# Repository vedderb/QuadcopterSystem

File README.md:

# The SP Quadcopter System

This is the source code and hardware design for a quadcopter system that was developed at SP Technical Research Institute of Sweden in the department of electronics as a demonstrator within the EU Projects KARYON and PROWESS.

Figure 1 shows an overview of the quadcopter system and how everything is connected.

The system consists of:

* Quadcopters
	- We have used up to 4 quadcopters simultaneously.
	
* [Anchors](#anchors)
	- For localization in GNSS-denied areas.
	- 2, 3 or 4 anchors can be used. When 4 anchors are used, the system can still operate if at least one of them or at most two of them fail due to redundancy.
	
* A Linux computer with two [stm32-bv motes](http://vedder.se/2013/04/cc2520-and-stm32-rf-boards/).
	- [QuadcopterTool](#quadcoptertool) is used for real time display and sending control commands to the quadcopters.
	- A border router is used to synchronize the clocks of all quadcopters and [anchors](#anchors) to microsecond level for ultrasound localization and TDMA communication.

* A [simulator](#coptersim) for the quadcopter system
	- The quadcopters and the localization system are simulated.
	- Can send the state of the simulation over UDP to [QuadcopterTool](#quadcoptertool) for visualization.
	- Cooperative collision avoidance is implemented in the simulator.

The following parts are included with this repository:

* **Embedded** - software running on the microcontrollers of the quadcopter system.
	- **border_router_clock_sync** - A contiki border router that also sends out clock synchronization packets (running on *stm32-bv with Contiki* in the next Figure).
	- **QuadcopterMain** - Main control software for the quadcopters (running on the *Mainboard*).
	- **Range** - Software for the *Ranging Board* and the anchors.
	- **Receiver** - Running on *stm32-bv with ChibiOS* in the next Figure and on a modified remote controller.
	- **Lib** - ChibiOS and Contiki
* **Linux** - software running on a GNU/Linux distribution (e.g. Ubuntu) for configuration, control and simulation.
	- **CopterSim** - A [simulation library](#coptersim) for the quadcopter system.
	- **CopterSimGui** - Graphical user interface for the [CopterSim](#coptersim) library
	- **FaultCheck** - Fault Injection Library used in [CopterSim](#coptersim) and [CopterSimGui](#coptersimgui)
	- **magnetometer_calibration** - Octave scripts for soft and hard iron compensation on the magnetometer.
	- **QuadcopterTool** - Graphical user interface for control and real time visualization of the quadcopter platform.
	- *build* - Script for building everything.
	- *clean* - Script for removing all built files.
	- *set_env* - Script used by the other scripts for setting the required environment variables.
	- *start_QuadcopterTool* - Script for starting [QuadcopterTool](#quadcoptertool).
	- *start_sim* - Script for starting [CopterSimGui](#coptersimgui) (that uses [CopterSim](#coptersim) and FaultCheck) and [QuadcopterTool](#quadcoptertool) for visualizing the simulation.
* **Hardware** - hardware design files
	- **MainBoard** - Design files for the MainBoard and Ranging Board PCBs
* **Documentation**
	- **Figures** - The figures in the documentation.
	- **Figures_pdf_png** - Png versions of all PDF files for including them in markdown
	- **PDF** - The documentation rendered as PDF files.
	- *conv_png* - Script for converting all PDF figures to PNG images.
* *build_doc* - Script for generating PDF files of the documentation.

A tutorial on how to get everything running can be found [here](Tutorial.md) (or [here](Tutorial.pdf) as pdf).

## Hardware on each Quadcopter

The hardware architecture on each quadcopter is shown in Figure 2.

Each quadcopter has two custom hardware-wise identical computing nodes connected over CAN-bus. The schematic and hardware layout, as well as the source code, for these computing nodes is included with this repository.

The Mainboard uses the [ChibiOS 3.x](http://www.chibios.org) RTOS, and runs the attitude control loop, position estimation, position control and interfaces with [QuadcopterTool](#quadcoptertool) over its radio link. The motors are connected to the Mainboard. More details about the software on the Mainboard can be found in the section [Mainboard Software](#mainboard-software).

The Ranging Board (RB) runs a [custom port](http://vedder.se/2013/10/a-contiki-port-for-my-custom-cc2520stm32f4-boards/) of [Contiki OS](http://www.contiki-os.org/) and is responsible for localization. The RB has a synchronized clock with the [anchors](#anchors) (provided by the border router) and measures the distance to them using the Time of Flight of ultrasound pulses sent from the anchors. In order to reject noise, the pulses are modulated using the sinc function and identified using cross correlation on sampled signal on the RB. An ultrasound height sensor is also connected to the RB that measures the distance from the quadcopter to the ground. All measured distances and the synchronized clock are sent over CAN-bus to the Mainboard for processing. Notice that the quadcopters can be controller manually without connecting the ranging board if desired.

A photo of the Main Board is shown in Figure 3.

## Mainboard Software
The important software on the MainBoard consists of the following parts:

**actuator**  
Translates throttle, roll, pitch and yaw output to commands for the motors. Compensation for varying input is also applied here.

**broadcast**  
Broadcast status and safety messages to the other quadcopters and to [QuadcopterTool](#quadcoptertool). The status message, used by [QuadcopterTool](#quadcoptertool), contains:

* Quadcopter ID
* Firmware Version
* Position (X, Y, Z)
* Attitude (roll, pitch, yaw)
* Velocity (vx, vy)
* Battery voltage
* Voltages sampled on the ADC port

The safety message (which will not be covered in detail in this description yet) contains:

* Quadcopter ID
* Local level of service
* Global level of service

To not get interference, these messages are sent out using TDMA based on the quad ID and the global clock provided by the ranging board.

**control**  
The attitude control loop.

**mpu9150** and **MahonyAHRS**  
Reading and processing of the accelerometer, gyroscope and magnetometer signals to calculate the filtered attitude of the quadcopter.

**navigation**  
The position control loop.

**pos**  
Position estimation based on the quadcopter attitude, [anchor](#anchors) readings and the motor power output (which for now is assumed to be 1g vertical acceleration).

**safety**  
Level of service calculation of the quadcopter (local) and all quadcopters (global).

**packet_handler**  
The communication protocol between QuadcopterTool and the quadcopters.

**Makefile**  
A makefile for building the software on the mainboard.

## QuadcopterTool

QuadcopterTool is a GUI to visualize and send commands to the quadcopter system. The main control page is shown in Figure 4. There are several pages for control, configuration and visualization, and the lower part of QuadcopterTool shows which quadcopters are sent status messages the past second together with their firmware version and battery level.

Figure 5 shows how the raw accelerometer, gyroscope and magnetometer values are plotted in real time in QuadcopterTool.

Figure 6 shows how one quadcopter is displayed on a map in real time in QuadcopterTool. 4 [anchors](#anchors) are also shown and a red bounding box where the quadcopter is allowed to fly. The [anchor](#anchors) positions and the bounding box can be edited and uploaded to the quadcopters from QuadcopterTool for the localization to work.

## Anchors

The quadcopter system uses anchors that send ultrasound pulses to the quadcopters for measuring the distance to them. This is done based on the time of flight of the ultrasound pulses which can be measured by having a synchronized clock between the quadcopters and anchors. This system is used for localization in GNSS-denied areas. A photo of the anchors is shown in Figure 7.

Figure 8 shows three quadcopters, three anchors and the distances measured between them. The quadcopters know the locations of all anchors, which are configured via [QuadcopterTool](#quadcoptertool).

To reject noise, the ultrasound pulses are modulated sinc functions and the Ranging Board does cross correlation between the samples signal and the expected pulse shape. Figure 9 shows the raw sampled signal and the cross correlation result when measuring a distance of around 10m. It can be seen that the cross correlation rejects almost all noise until the actual pulse (and its reflections) is received. To get the direct path and not a reflection that might be stronger, the Ranging Boards looks for the first top above a certain threshold and not the highest top.

If no pulse above with an amplitude above the threshold is received, the measurement from that anchor is ignored. This way, the system can still operate when one or two anchors fail (if there are enough anchors from the beginning).

## CopterSim

CopterSim is a library written in C++ with an interface where quadcopters can be added, removed, or commanded to move. A block diagram of the simulator is shown in Figure 10.

The block named *CopterSim* has a list of *CopterModels* and a list of line segments that represent static terrain. For every time-step dt, CopterSim executes the state update function for each CopterModel and checks for collisions between all CopterModels and the static terrain. When a collision occurs, the simulation is halted and the position of the collision is reported. When a CopterModel is added to the simulation, CopterSim will upload the list of terrain to it and broadcast perceived position state messages from it to the other CopterModels and vice versa. This broadcast is done between all quadcopters every communication time interval and the messages are passed through the communication channel of FaultCheck, where communication faults can be injected.

The *CopterModel* block runs the same source code for position and velocity estimation as the implementation on the embedded implementation. The attitude is updated from the movement command with a similar response to that of the actual hardware, and the golden run (the fault-free position and velocity state) is updated based on this attitude. In addition to the true position state for each quadcopter, CopterModel also updates the perceived position for them. For the perceived position, we have added FaultCheck probes to the various state variables where faults can be injected. As long as no fault is activated, the true and perceived position will be the same. As soon as we activate faults, the positions will drift apart.

In order to compensate for faults and thus position drift, the perceived position has to be estimated using ultrasound sensor readings. CopterModel is aware of all anchors and emulates ultrasound-sensor readings based on the true position state and the anchor positions, with the same rate as they are received on the hardware quadcopters. These readings are passed to the correction part of the position-estimation algorithm, which then corrects the position.

Every CopterModel has a block named ITS station, which builds and updates a Local Dynamic Map (LDM) that contains all other quadcopters and their states as it receives messages from them. The ITS station also keeps track of the terrain (received from CopterSim) and runs a collision-avoidance mechanism based on the LDM. Since the ITS-station operates on the perceived position of all quadcopters, it is important that the position-estimations algorithm performs well when there are faults present, and that safety margins are large enough to cope with an inaccurate perceived position.

### Collision Avoidance in the Simulator
We perform collision avoidance by placing risk contours around quadcopters and static objects from the perspective of every quadcopter, and steering away if the risk contours overlap with the comfort zone of the quadcopter. This means that the risk contours are not a global state, but different from every quadcopter's perspective based on its relative velocity to the object and when the positions of other quadcopters were last received. The comfort zone is represented as a circle placed around the quadcopter with a radius that is calculated based on the confidence of the position estimation.

The risk contours are two-dimensional and represented as ellipses with width, height and rotation, and they are sized and rotated based on the squared relative velocity vector to the quadcopters/objects they surround. To share knowledge about the position of all quadcopters, the quadcopters broadcast this information, one at a time, to the rest of the fleet. When a quadcopter receives a position update from another quadcopter, it will update its LDM, which contains the positions of all other known quadcopters and the surrounding terrain, with this information. Between the position updates, the risk contours around other quadcopters will be moved and reshaped based on the velocity that the other quadcopters had when their positions were last received. When an overlap between the comfort zone of a quadcopter and a risk contour occurs, the collision-avoidance mechanism will take over control and steer away from the overlapping risk contour in the opposing direction. If there are several overlaps at the same time, a vector will be calculated from a weighted sum of all overlapping risk contours and their relative direction, and used to steer away from the collision.

## CopterSimGui

CopterSimGui is a GUI for controlling the [CopterSim](#coptersim) library. It supports the interfaces of CopterSim and also has some hard coded scenarios. All simulated quadcopters are shown in a list together with their actual and perceived position. There is also an interface to control the probes of the FaultCheck library and do fault injection in the simulation. A screenshot of CopterSimGui is shown Figure 11.

The connection between CopterSim, FaultCheck, CopterSimGui and QuadcopterTool is shown in Figure 12. CopterSimGui links to the CopterSim library, which links to the FaultCheck library. The CopterSim library sends the state of the simulation to QuadcopterTool over UDP so that the simulation can be visualized in real time using the same drawing interface as for the hardware quadcopters.

Figure 13 shows a screenshot of [QuadcopterTool](#quadcoptertool) where a CopterSim simulation with many quadcopters is visualized in real time. The quadcopter with the small circle around it (which is the comfort zone) is the selected one and the red circles are the risk contours around other quadcopters that overlap with the comfort zone of the selected quadcopter. All risk contours in that screenshot are from the perspective of the selected quadcopter.

QuadcopterTool can also show the which faults are injected for different quadcopters and the position and velocity errors caused by these faults as shown in Figure 14.

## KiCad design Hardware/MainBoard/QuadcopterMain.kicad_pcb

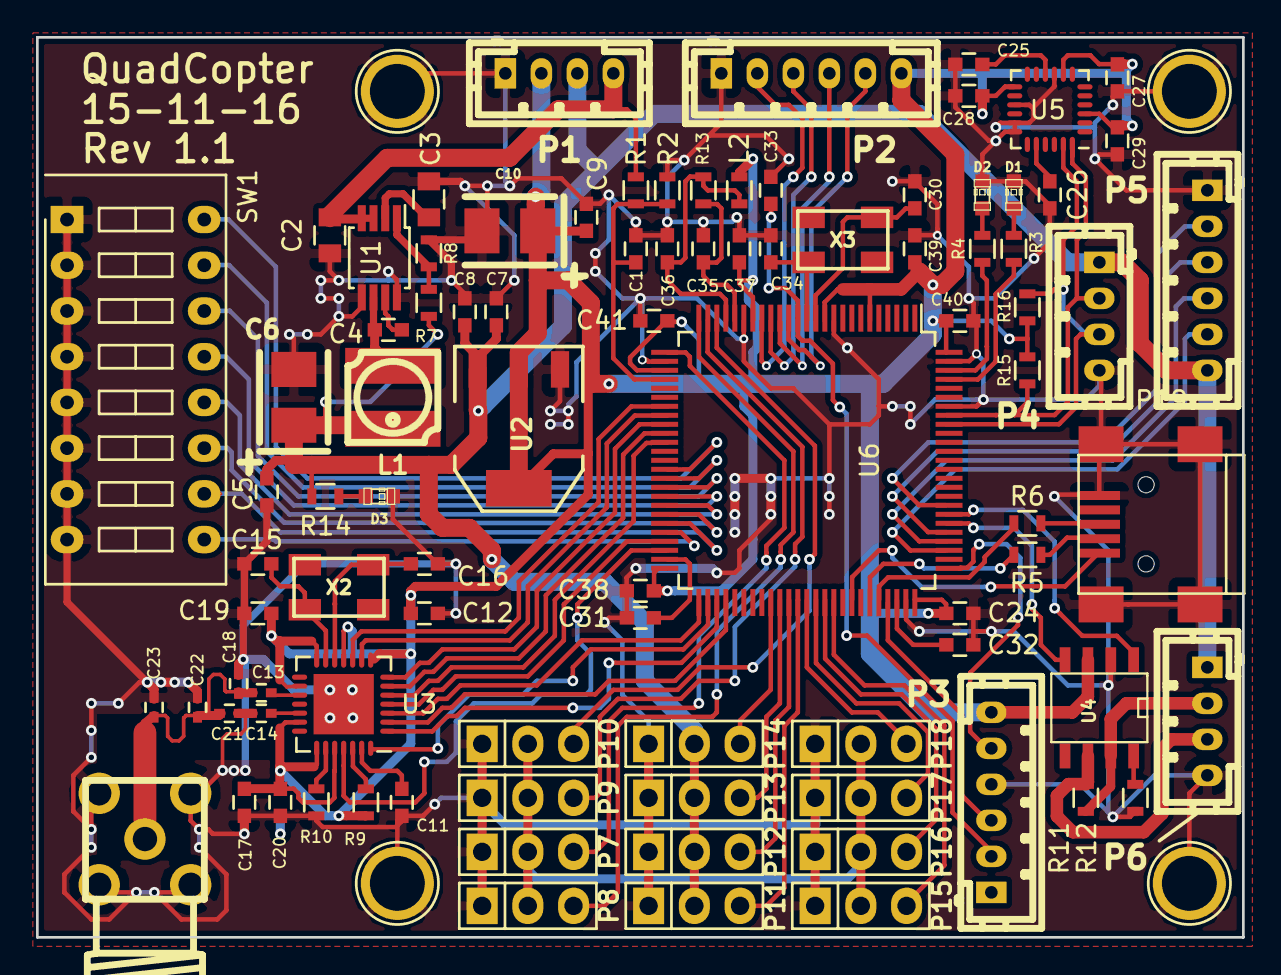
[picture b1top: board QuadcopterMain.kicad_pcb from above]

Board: 2 copper layers, 67.0 x 50.0 mm, 91 parts (0 on the bottom side), 84 nets.

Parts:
C1, C24: 1u; C_0603
C2, C3: 2.2u; C_0805
C4, C11, C12, C15, C17, C26, C33: 100n; C_0603
C5, C7, C8, C9, C25, C27, C28, C29, C31, C32, C35, C36, C37, C38, C39, C40, C41: 2.2u; C_0603
C6, C10: 100u; TantalC_SizeB_EIA-3528_Reflow
C13: 39p; C_0402
C14: 82p; C_0402
C16, C19: 27p; C_0603
C18, C22: 1.8p; C_0402
C20: 10u; C_0603
C21: 1.5p; C_0402
C23: 1p; C_0402
C30, C34: 15p; C_0603
D1: RED; LED-0603
D2: GREEN; LED-0603
D3: BLUE; LED-0603
J1: SMA; sma_90_r300.124.403
L1: 22U; inductor_smd_4.8x2.8mm
L2: INDUCTOR; R_0603
P1: POWER; b4b-ph-kl
P2: ADC_GPIO; b6b-ph-kl
P3: SWD; b6b-ph-kl
P4: I2C; b4b-ph-kl
P5: UART/SPI; b6b-ph-kl
P6: CAN; b4b-ph-kl
P7, P8, P9, P10, P11, P12, P13, P14, P15, P16, P17, P18: SERVO_IO; Pin_Header_Straight_1x03
P19: USB_OTG; USB_Mini-B
R1, R8, R9, R12: 10k; R_0603
R2, R15, R16: 2.2k; R_0603
R3, R4, R14: 330R; R_0603
R5, R6: 22R; R_0603
R7: 52k; R_0603
R10: 56k; R_0603
R11: NI; R_0603
R13: 47R; R_0603
SW1: ADDRESS; SW_DIP_x8_Slide
U1: MCP16311/2; MSOP-8_3x3mm_Pitch0.65mm
U2: NCP1117ST33T3G; SOT-223
U3: CC2520; QFN-28-1EP_5x5mm_Pitch0.5mm
U4: SN65HVD232; SOIC-8-W
U5: MPU9150; QFN-24-1EP_4x4mm_Pitch0.5mm
U6: STM32F40X_LQFP100; LQFP-100_14x14mm_Pitch0.5mm
X2: 32M; Crystal_5x3mm
X3: CRYSTAL; Crystal_5x3mm

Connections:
+5V: C5.2, C6.1, C7.2, C8.2, L1.1, P1.3, P4.1, P5.6, P6.1, P7.2, P8.2, P9.2, P10.2, P11.2, P12.2, P13.2, P14.2, P15.2, P16.2, P17.2, P18.2, R7.2, R14.2, U2.3
+BATT: C2.2, P1.4, R1.1, U1.3, U1.4
/CAN/CANH: P6.2, R11.1, U4.7
/CAN/CANL: P6.3, R11.2, U4.6
/CAN/CAN_RX: U4.4, U6.81
/CAN/CAN_TX: U4.1, U6.82
/CC2520/CC_CS_N: U3.3, U6.51
/CC2520/CC_GPIO0: U3.10, U6.32
/CC2520/CC_GPIO1: U3.9, U6.33
/CC2520/CC_GPIO2: U3.7, U6.34
/CC2520/CC_GPIO3: U3.6, U6.35
/CC2520/CC_GPIO4: U3.5, U6.36
/CC2520/CC_GPIO5: U3.4, U6.47
/CC2520/CC_RESET: U3.25, U6.48
/CC2520/CC_SCLK: U3.28, U6.52
/CC2520/CC_SI: U3.2, U6.54
/CC2520/CC_SO: U3.1, U6.53
/Microcontroller/NRST: C33.2, P3.2, U6.14
/Microcontroller/PA0_TIM5_CH1: P10.3, U6.23
/Microcontroller/PA1_TIM5_CH2: P9.3, U6.24
/Microcontroller/PA2_TIM5_CH3: P8.3, U6.25
/Microcontroller/PA3_TIM5_CH4: P7.3, U6.26
/Microcontroller/PA4_ADC123_IN4: C1.1, R1.2, R2.1, U6.29
/Microcontroller/PB6_SCL: P4.3, R16.2, U5.23, U6.92
/Microcontroller/PB7_SDA: P4.2, R15.2, U5.24, U6.93
/Microcontroller/PC0_ADC123_IN10: P2.5, U6.15
/Microcontroller/PC1_ADC123_IN11: P2.4, U6.16
/Microcontroller/PC2_ADC123_IN12: P2.3, U6.17
/Microcontroller/PC3_ADC123_IN13: P2.2, U6.18
/Microcontroller/PC6_TIM3_CH1: P18.3, U6.63
/Microcontroller/PC7_TIM3_CH2: P17.3, U6.64
/Microcontroller/PC8_TIM3_CH3: P16.3, U6.65
/Microcontroller/PC9_TIM3_CH4: P15.3, U6.66
/Microcontroller/PC10_UART34TX_SPI3SCK: P5.5, U6.78
/Microcontroller/PC11_UART34RX_SPI3MISO: P5.4, U6.79
/Microcontroller/PC12_SPI3MOSI: P5.3, U6.80
/Microcontroller/PD2: P5.2, U6.83
/Microcontroller/PD12_TIM4_CH1: P14.3, U6.59
/Microcontroller/PD13_TIM4_CH2: P13.3, U6.60
/Microcontroller/PD14_TIM4_CH3: P12.3, U6.61
/Microcontroller/PD15_TIM4_CH4: P11.3, U6.62
/Microcontroller/PE0: R3.2, U6.97
/Microcontroller/PE1: R4.2, U6.98
/Microcontroller/PE8: SW1.16, U6.39
/Microcontroller/PE9: SW1.15, U6.40
/Microcontroller/PE10: SW1.14, U6.41
/Microcontroller/PE11: SW1.13, U6.42
/Microcontroller/PE12: SW1.12, U6.43
/Microcontroller/PE13: SW1.11, U6.44
/Microcontroller/PE14: SW1.10, U6.45
/Microcontroller/PE15: SW1.9, U6.46
/Microcontroller/SWCLK: P3.5, U6.76
/Microcontroller/SWDIO: P3.3, U6.72
/Microcontroller/USB_DM: R5.2, U6.70
/Microcontroller/USB_DP: R6.2, U6.71
/Microcontroller/USB_VP: P19.1, U6.68
GND: C1.2, C2.1, C3.1, C5.1, C6.2, C7.1, C8.1, C9.1, C10.2, C11.1, C12.1, C14.2, C15.1, C16.2, C17.1, C18.1, C19.2, C20.1, C21.2, C22.1, C23.1, C24.2, C25.2, C26.2, C27.2, C28.2, C29.2, C30.2, C31.2, C32.2, C33.1, C34.2, C35.1, C36.2, C37.1, C38.1, C39.1, C40.1, C41.1, D1.2, D2.2, D3.2, J1.2, P1.1, P2.1, P3.4, P4.4, P5.1, P6.4, P7.1, P8.1, P9.1, P10.1, P11.1, P12.1, P13.1, P14.1, P15.1, P16.1, P17.1, P18.1, P19.5, P19.6, R2.2, R8.1, R10.2, R12.2, SW1.1, SW1.2, SW1.3, SW1.4, SW1.5, SW1.6, SW1.7, SW1.8, U1.5, U1.8, U2.1, U3.29, U4.2, U5.9, U5.15, U5.17, U5.18, U6.10, U6.20, U6.27, U6.74, U6.94, U6.99
unnamed: C3.2, U1.2
unnamed: C4.1, L1.2, U1.6
unnamed: C4.2, U1.7
unnamed: C11.2, U3.27
unnamed: C13.1, U3.17
unnamed: C14.1, U3.19
unnamed: C16.1, U3.12, X2.1
unnamed: C19.1, U3.13, X2.2
unnamed: C25.1, U5.10
unnamed: C26.1, U5.20
unnamed: C30.1, U6.12, X3.1
unnamed: C31.1, U6.49
unnamed: C32.1, U6.73
unnamed: C34.1, U6.13, X3.2
unnamed: C35.2, R13.1, U6.21
unnamed: C36.1, L2.2, R13.2, U6.22
unnamed: D1.1, R3.1
unnamed: D2.1, R4.1
unnamed: D3.1, R14.1
unnamed: P19.2, R5.1
unnamed: P19.3, R6.1
unnamed: R7.1, R8.2, U1.1
unnamed: R9.2, U3.26
unnamed: R10.1, U3.23
unnamed: R12.1, U4.8
TL2: C13.2, C18.2, C21.1, C22.2, C23.2, J1.1
VCC: C9.2, C10.1, C12.2, C15.2, C17.2, C20.2, C24.1, C27.1, C28.1, C29.1, C37.2, C38.2, C39.2, C40.2, C41.2, L2.1, P1.2, P2.6, P3.6, R9.1, R15.1, R16.1, U2.2, U3.8, U3.11, U3.14, U3.16, U3.20, U3.22, U3.24, U4.3, U5.3, U5.8, U5.13, U6.6, U6.11, U6.19, U6.28, U6.50, U6.75, U6.100

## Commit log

2015-12-16 Added all files
